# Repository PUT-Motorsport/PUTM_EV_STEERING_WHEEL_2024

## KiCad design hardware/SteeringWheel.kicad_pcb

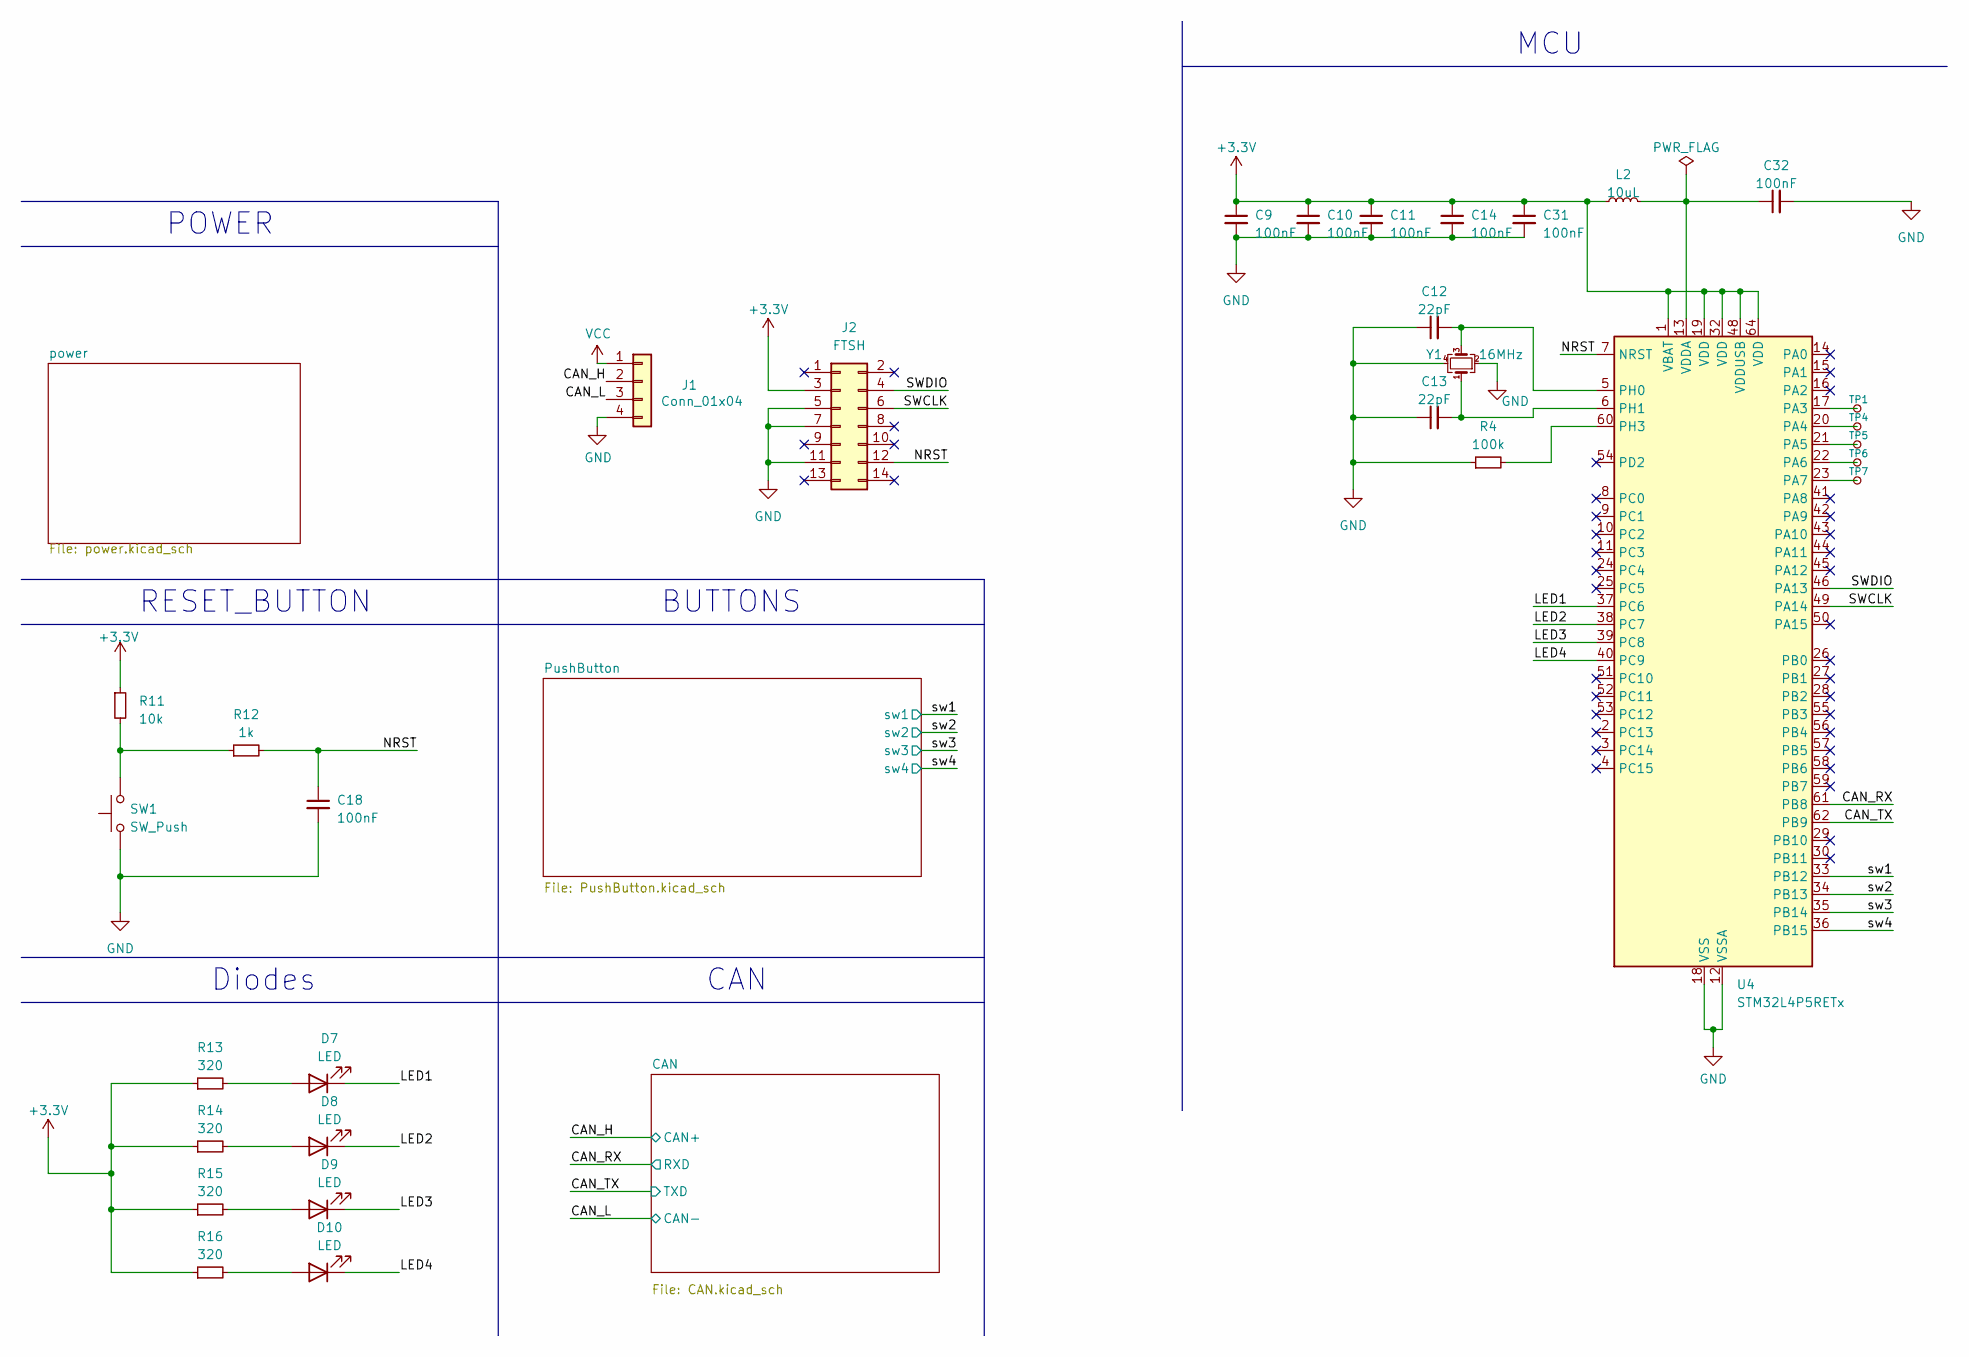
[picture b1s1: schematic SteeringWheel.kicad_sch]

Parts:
C9, C10, C11, C14, C18, C31, C32: 100nF; C_0603_1608Metric
C12, C13: 22pF; C_0603_1608Metric
D7, D8, D9, D10: LED; LED_0603_1608Metric
J1: Conn_01x04; JST_XH_B4B-XH-A_1x04_P2.50mm_Vertical
J2: FTSH; FTSH-107-XX-YYY-DV-K-A; Mouser Part Number 200-FTSH10701LDVKA
L2: 10uL; L_0603_1608Metric
R4: 100k; R_0603_1608Metric
R11: 10k; R_0603_1608Metric
R12: 1k; R_0603_1608Metric
R13, R14, R15, R16: 320; R_0603_1608Metric
SW1: SW_Push; SW_SPST_B3U-1000P
TP1, TP4, TP5, TP6, TP7: TestPoint_Small; TestPoint_Pad_D1.0mm
U4: STM32L4P5RETx; LQFP-64_10x10mm_P0.5mm
Y1: 16MHz; Crystal_SMD_Abracon_ABM8G-4Pin_3.2x2.5mm

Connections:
+3.3V: C9.1, C10.1, C11.1, C14.1, C31.1, J2.3, L2.1, R11.1, R13.1, R14.1, R15.1, R16.1, U4.1 (VBAT), U4.19 (VDD), U4.32 (VDD), U4.48 (VDDUSB), U4.64 (VDD); also elsewhere on the board
/CAN_RX: U4.61 (PB8); also elsewhere on the board
/CAN_TX: U4.62 (PB9); also elsewhere on the board
/LED1: D7.1 (K), U4.37 (PC6)
/LED2: D8.1 (K), U4.38 (PC7)
/LED3: D9.1 (K), U4.39 (PC8)
/LED4: D10.1 (K), U4.40 (PC9)
/NRST: C18.1, J2.12, R12.2, U4.7 (NRST)
/SWCLK: J2.6, U4.49 (PA14)
/SWDIO: J2.4, U4.46 (PA13)
/sw1: U4.33 (PB12); also elsewhere on the board
/sw2: U4.34 (PB13); also elsewhere on the board
/sw3: U4.35 (PB14); also elsewhere on the board
/sw4: U4.36 (PB15); also elsewhere on the board
GND: C9.2, C10.2, C11.2, C12.1, C13.1, C14.2, C18.2, C31.2, C32.2, J2.5, J2.7, J2.11, R4.1, SW1.1, U4.12 (VSSA), U4.18 (VSS), U4.31 (VSS), U4.47 (VSS), U4.63 (VSS), Y1.2, Y1.4; also elsewhere on the board
unnamed: D7.2 (A), R13.2
unnamed: D8.2 (A), R14.2
unnamed: D9.2 (A), R15.2
unnamed: D10.2 (A), R16.2
unnamed: R11.2, R12.1, SW1.2
unnamed: TP1.1, U4.17 (PA3)
unnamed: TP4.1, U4.20 (PA4)
unnamed: TP5.1, U4.21 (PA5)
unnamed: TP6.1, U4.22 (PA6)
unnamed: TP7.1, U4.23 (PA7)
unnamed: C12.2, U4.5 (PH0), Y1.3
unnamed: C13.2, U4.6 (PH1), Y1.1
unnamed: R4.2, U4.60 (PH3)
unnamed: C32.1, L2.2, U4.13 (VDDA)

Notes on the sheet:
RESET_BUTTON
CAN
BUTTONS
POWER
Diodes
MCU

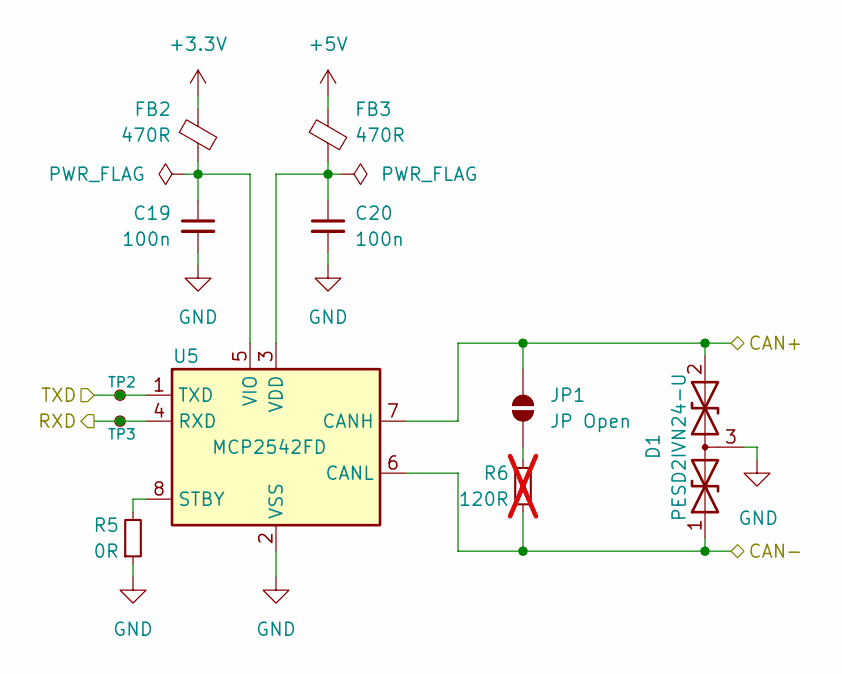
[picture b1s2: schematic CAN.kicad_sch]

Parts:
C19, C20: 100n; C_0603_1608Metric
D1: PESD2IVN24-U; SOT-323_SC-70
FB2, FB3: 470R; L_0603_1608Metric
JP1: JP Open; SolderJumper-2_P1.3mm_Open_Pad1.0x1.5mm
R5: 0R; R_0603_1608Metric
R6: 120R; R_0603_1608Metric; not fitted
TP2, TP3: TestPoint_Small; TestPoint_Pad_D1.0mm
U5: MCP2542FD; DFN-8-1EP_3x3mm_P0.65mm_EP1.55x2.4mm

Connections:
+3.3V: FB2.1; also elsewhere on the board
+5V: FB3.1; also elsewhere on the board
/CAN_H: D1.2 (A2), JP1.2 (B), U5.7 (CANH); also elsewhere on the board
/CAN_L: D1.1 (A1), R6.1, U5.6 (CANL); also elsewhere on the board
/CAN_RX: TP3.1, U5.4 (RXD); also elsewhere on the board
/CAN_TX: TP2.1, U5.1 (TXD); also elsewhere on the board
GND: C19.2, C20.2, D1.3 (common), R5.1, U5.2 (VSS), U5.9 (VSS); also elsewhere on the board
unnamed: JP1.1 (A), R6.2
unnamed: R5.2, U5.8 (STBY)
unnamed: C20.1, FB3.2, U5.3 (VDD)
unnamed: C19.1, FB2.2, U5.5 (VIO)

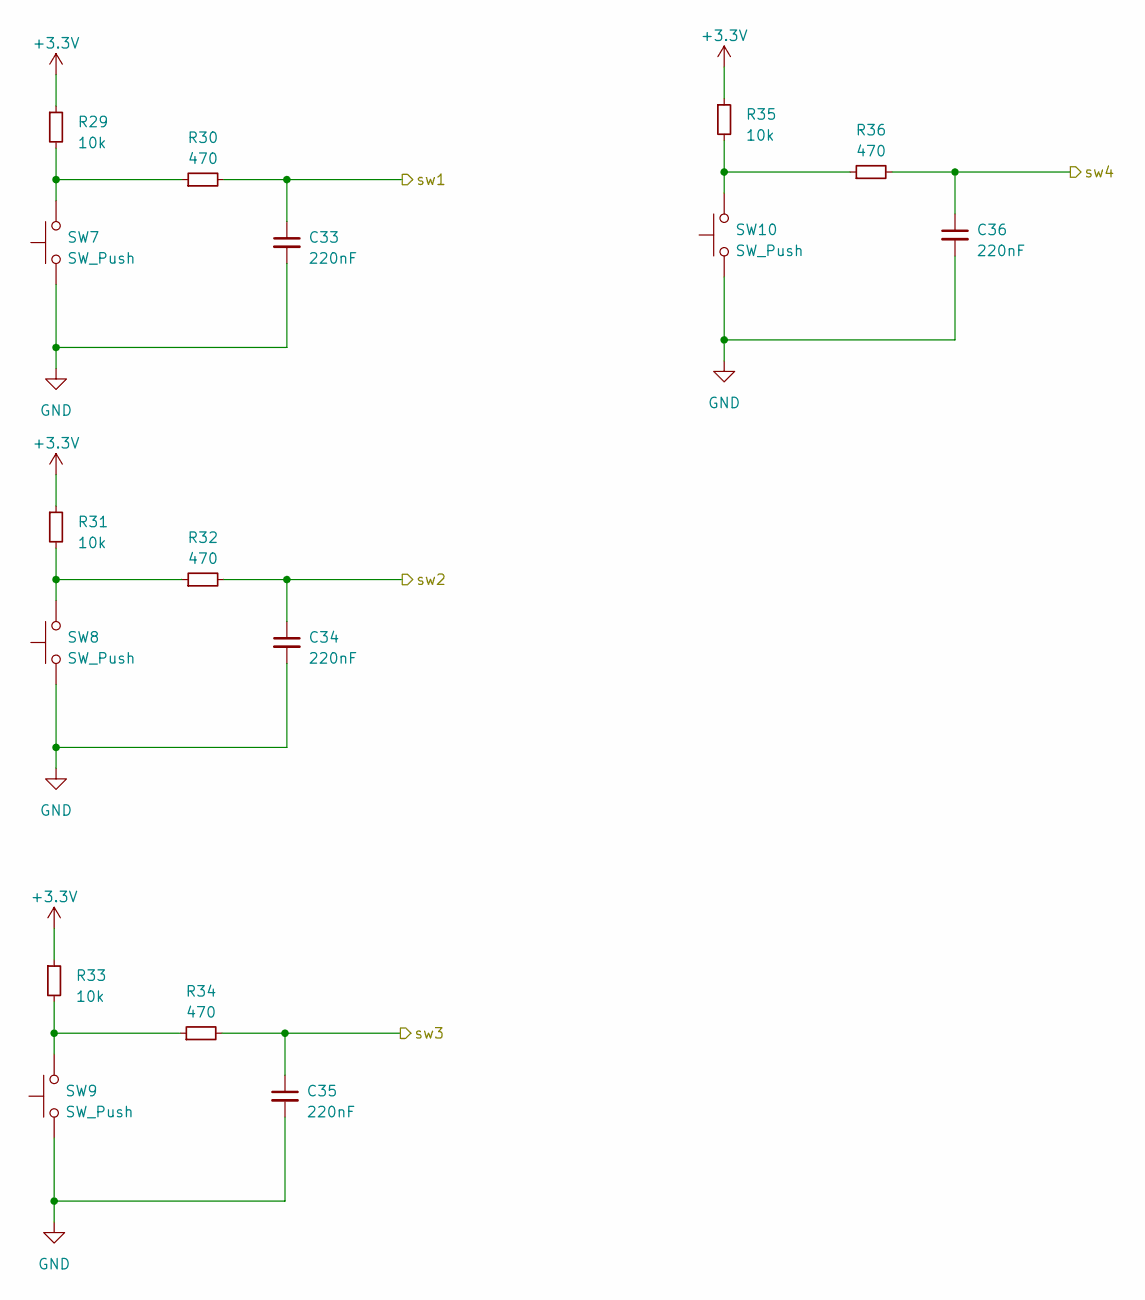
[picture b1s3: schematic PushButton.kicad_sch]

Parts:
C33, C34, C35, C36: 220nF; C_0603_1608Metric
R29, R31, R33, R35: 10k; R_0603_1608Metric
R30, R32, R34, R36: 470; R_0603_1608Metric
SW7, SW8, SW9, SW10: SW_Push; JST_XH_S2B-XH-A_1x02_P2.50mm_Horizontal

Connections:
+3.3V: R29.1, R31.1, R33.1, R35.1; also elsewhere on the board
/sw1: C33.1, R30.2; also elsewhere on the board
/sw2: C34.1, R32.2; also elsewhere on the board
/sw3: C35.1, R34.2; also elsewhere on the board
/sw4: C36.1, R36.2; also elsewhere on the board
GND: C33.2, C34.2, C35.2, C36.2, SW7.1, SW8.1, SW9.1, SW10.1; also elsewhere on the board
unnamed: R29.2, R30.1, SW7.2
unnamed: R31.2, R32.1, SW8.2
unnamed: R33.2, R34.1, SW9.2
unnamed: R35.2, R36.1, SW10.2

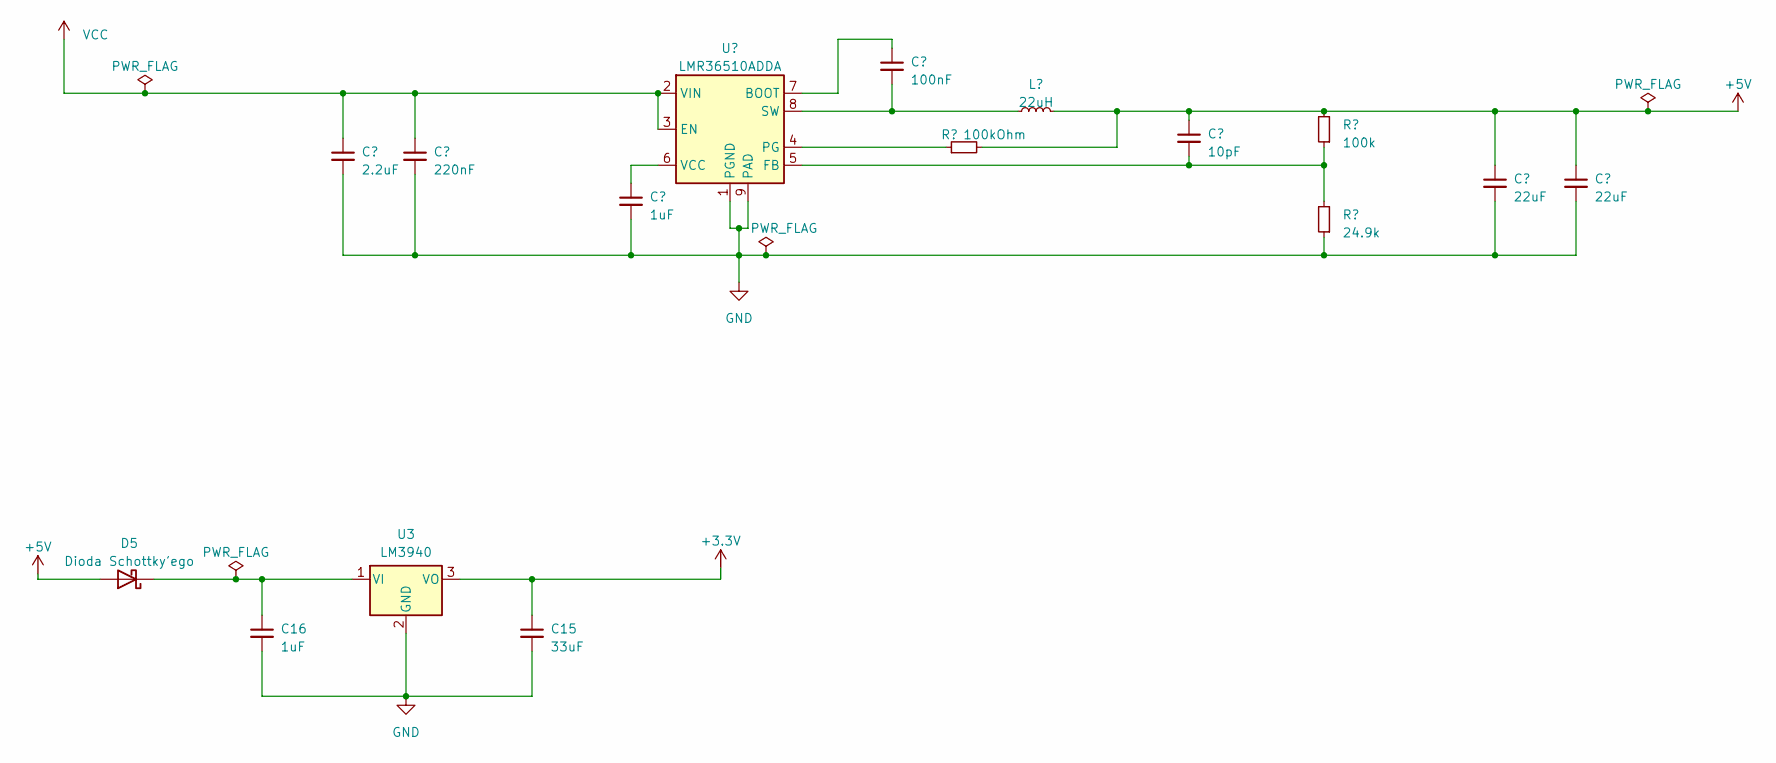
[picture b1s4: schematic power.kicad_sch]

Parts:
C1: 2.2uF; C_0805_2012Metric
C2: 220nF; C_0603_1608Metric
C3, C16: 1uF; C_0603_1608Metric
C4: 100nF; C_0603_1608Metric
C5: 10pF; C_0603_1608Metric
C6, C17: 22uF; C_0805_2012Metric
C15: 33uF; C_0603_1608Metric
D5: Dioda Schottky'ego; D_SOD-123
L1: 22uH; L_7.3x7.3_H4.5
R1: 100kOhm; R_0603_1608Metric
R2: 100k; R_0603_1608Metric
R3: 24.9k; R_0603_1608Metric
U2: LMR36510ADDA; Texas_HTSOP-8-1EP_3.9x4.9mm_P1.27mm_EP2.95x4.9mm_Mask2.4x3.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
U3: LM3940; SOT-223

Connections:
+3.3V: C15.1, U3.3 (VO); also elsewhere on the board
+5V: C5.1, C6.1, C17.1, D5.2 (A), L1.2, R1.2, R2.2; also elsewhere on the board
GND: C1.2, C2.2, C3.2, C6.2, C15.2, C16.2, C17.2, R3.1, U2.1 (PGND), U2.9 (PAD), U3.2 (GND); also elsewhere on the board
unnamed: C16.1, D5.1 (K), U3.1 (VI)
unnamed: C4.1, U2.7 (BOOT)
unnamed: C5.2, R2.1, R3.2, U2.5 (FB)
unnamed: R1.1, U2.4 (PG)
unnamed: C4.2, L1.1, U2.8 (SW)
unnamed: C3.1, U2.6 (VCC)
VCC: C1.1, C2.1, U2.2 (VIN), U2.3 (EN); also elsewhere on the board

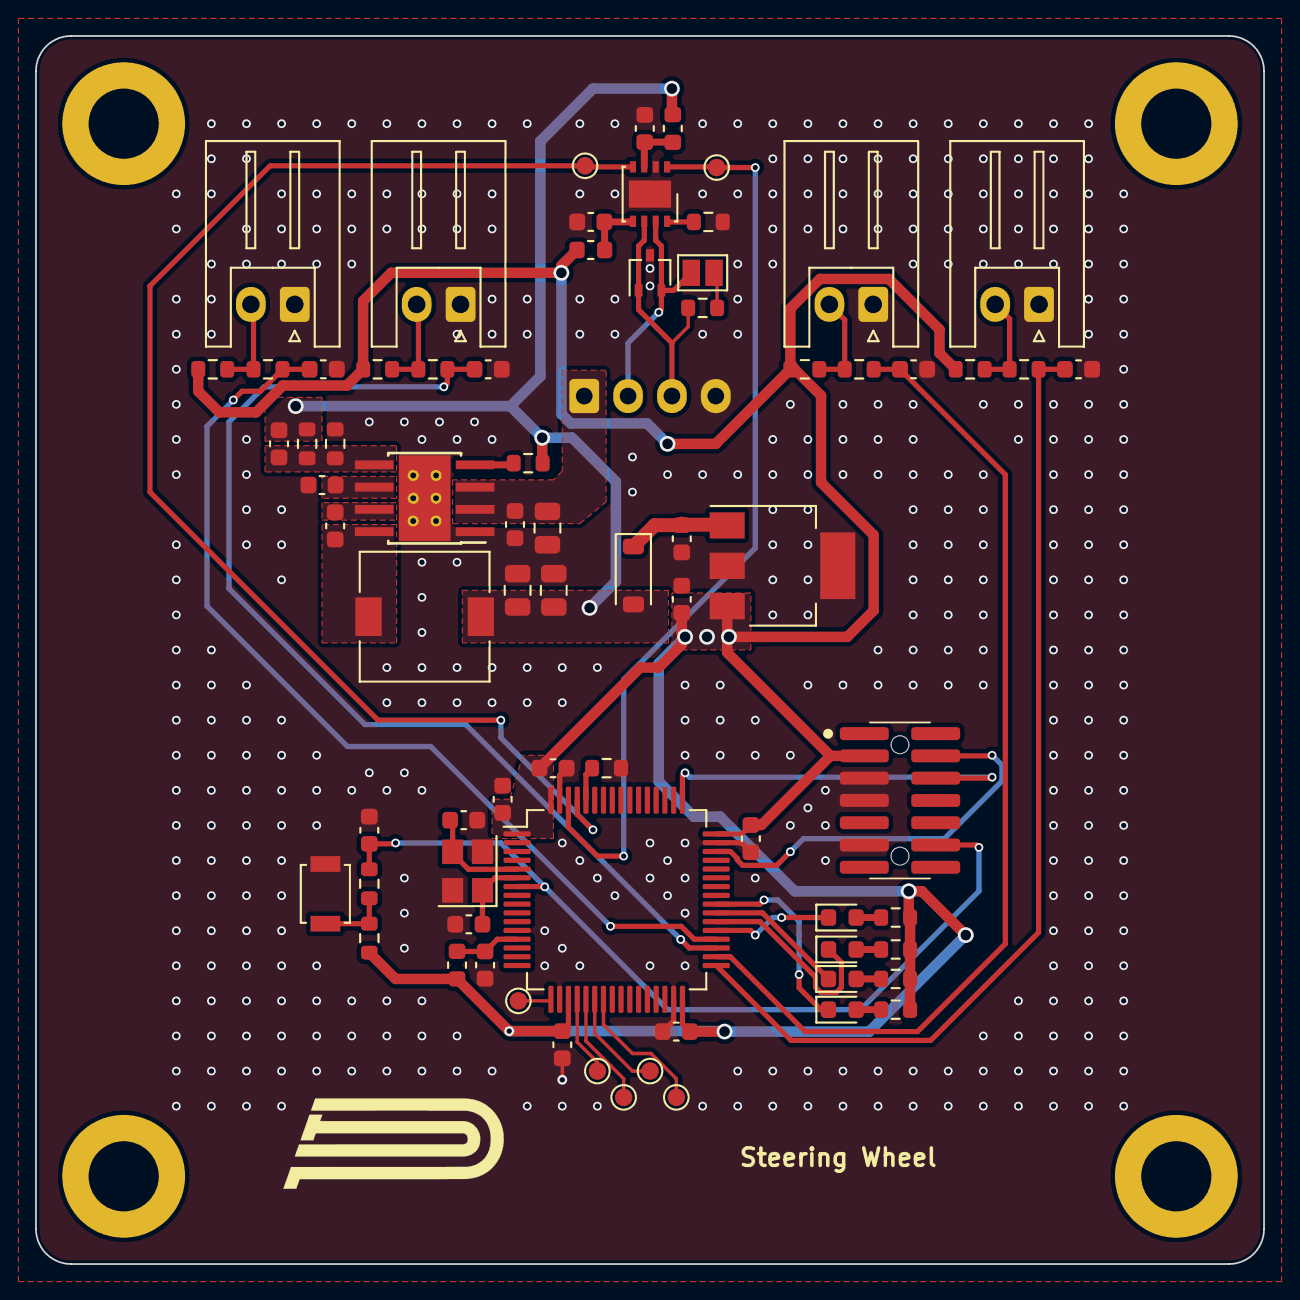
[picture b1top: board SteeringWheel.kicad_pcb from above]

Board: 2 copper layers, 70.0 x 70.0 mm, 74 parts (1 on the bottom side), 47 nets.

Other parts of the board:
JST1: Conn_01x04; JST_XH_B4B-XH-A_1x04_P2.50mm_Vertical

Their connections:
/CAN_H: JST1.2; also elsewhere on the board
/CAN_L: JST1.3; also elsewhere on the board
GND: JST1.4; also elsewhere on the board
VCC: JST1.1; also elsewhere on the board

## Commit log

2024-04-25 File structure added
    -working on layout
2024-04-25 Rename of the KiCad project and backups deleted
2024-04-25 Placement done
2024-04-25 Layout done
2024-04-25 Vias and adnotations update
2024-04-26 Fix minor issues
